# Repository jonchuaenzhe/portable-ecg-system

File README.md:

Jan 2020 - Dec 2020
# IoT-enabled Portable 12-Lead ECG System

12-Lead ECGs are usually bulky and mounted on carts. This project in collaboration with NUH Emergency Department developed a portable version of it which displayed ECG tracings on a web-app to increase the efficiency of clinicians and comfort of patients. Take a look at the video below for a short demo of the system.

https://user-images.githubusercontent.com/59247141/186677922-14ab5f33-408b-436f-be4c-0afafe76f2a2.mp4

## Device

The Schematics and Layout of the circuit board design can be viewed directly in the "device" folder as PDF files.

"main.cpp" contains the firmware for the device, which runs on an ESP32 chip. It requires some commonly used ESP32 libraries not included in the "device" folder.

## Web Dashboard

The "app" folder houses both the client and server components of the MERN stack.

### Installation

Install dependencies for frontend by entering the frontend folder and running:
```
yarn install
```
Install dependencies for backend by entering the backend folder and running:
```
npm install
```

### Running Locally

To start the frontend application, enter the frontend folder and run:
```
yarn start
```
This runs the app in the development mode. Open [http://localhost:3000](http://localhost:3000) to view it in the browser. The page will reload if you make edits. You will also see any lint errors in the console.

To start the backend application, enter the backend folder on a separate terminal and run:
```
npm dev
```

### Deploying

The entire stack is deployed using Docker. Docker images are uploaded onto DockerHub and `docker-compose.prd.yml` is uploaded onto the server. To deploy the application, ssh into the server and run the docker-compose file:
```
ssh root@128.199.106.255
docker-compose -f docker-compose.prd.yml up -d --build
```

This will create a "docker network" and attach the three running containers (consisting of the client listening at port `3000`, server listening at port `5000` and mongo database listening at port `27017` on `mongo`) to it.

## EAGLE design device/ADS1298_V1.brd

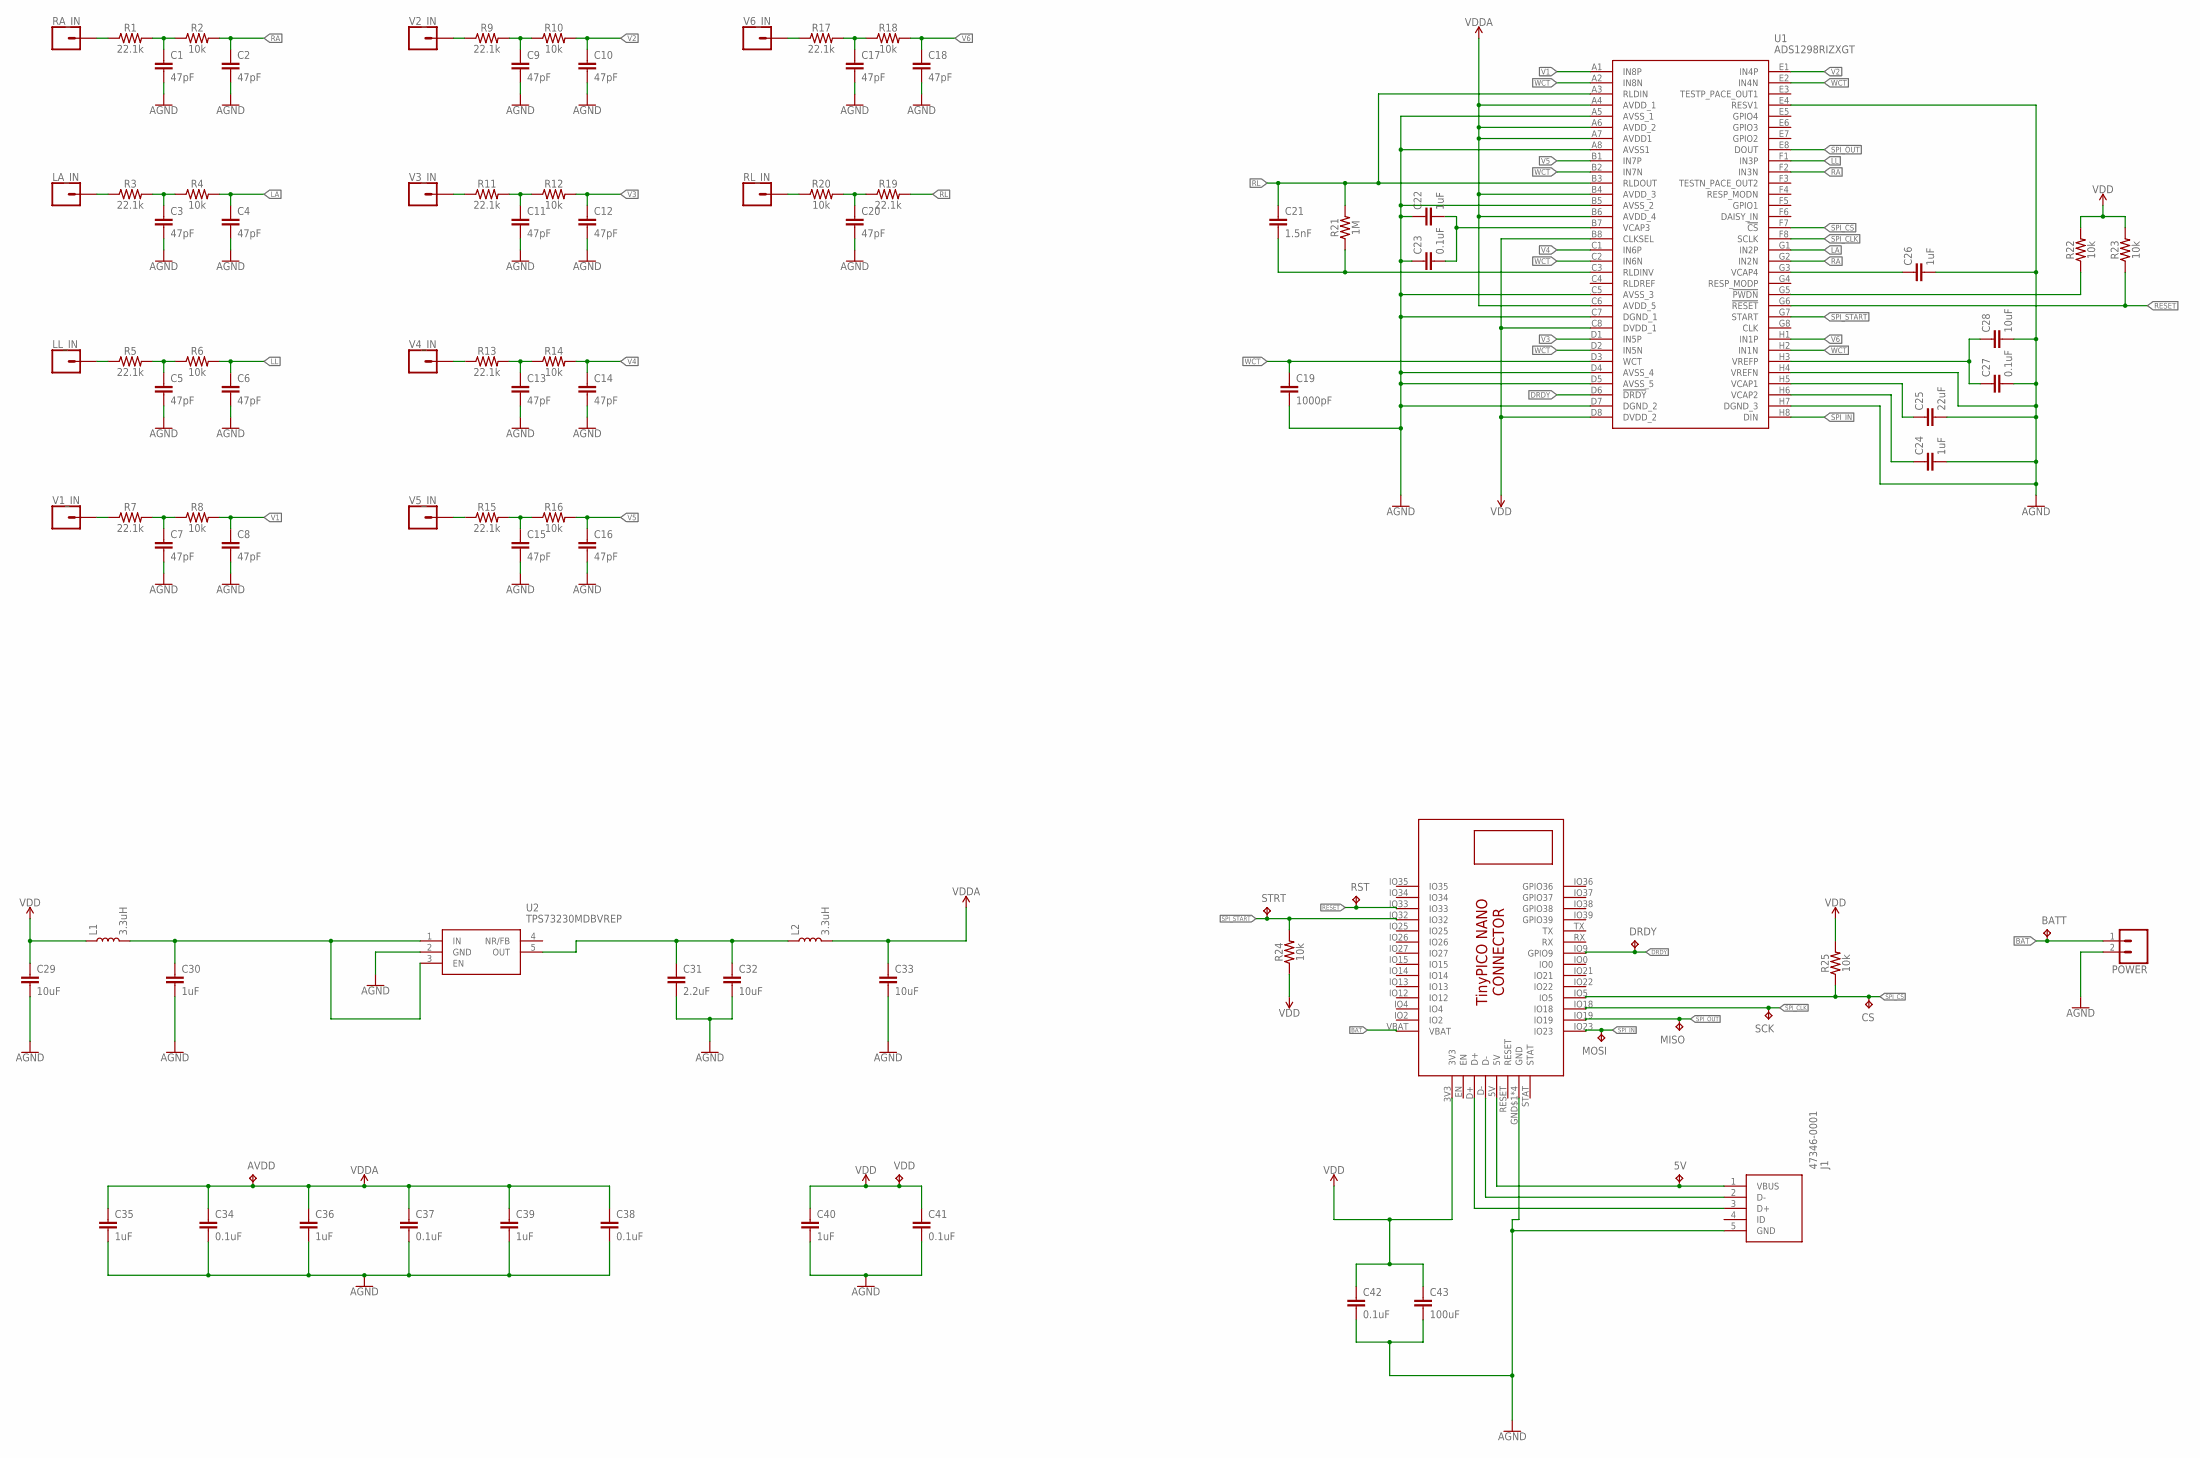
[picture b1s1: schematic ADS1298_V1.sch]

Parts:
5V: TPB1,27; B1,27
AVDD: TPB1,27; B1,27
BATT: TPB1,27; B1,27
C1, C2, C3, C4, C5, C6, C7, C8, C9, C10, C11, C12, C13, C14, C15, C16, C17, C18, C20: 47pF; 0603
C19: 1000pF; 0603
C21: 1.5nF; 0603
C22, C24, C26, C30, C35, C36, C39, C40: 1uF; 0603
C23, C27, C34, C37, C38, C41, C42: 0.1uF; 0603
C25: 22uF; 0805
C28, C29, C32, C33: 10uF; 0805
C31: 2.2uF; 0603
C43: 100uF; 0805
CS: TPB1,27; B1,27
DRDY: TPB1,27; B1,27
J1: 47346-0001
L1, L2: 3.3uH; 0805
LA_IN: CONN_01; 1X01
LL_IN: CONN_01; 1X01
MISO: TPB1,27; B1,27
MOSI: TPB1,27; B1,27
POWER: CONN_02; 1X02
R1, R3, R5, R7, R9, R11, R13, R15, R17, R19: 22.1k; 0603
R2, R4, R6, R8, R10, R12, R14, R16, R18, R20, R22, R23, R24, R25: 10k; 0603
R21: 1M; 0603
RA_IN: CONN_01; 1X01
RL_IN: CONN_01; 1X01
RST: TPB1,27; B1,27
SCK: TPB1,27; B1,27
STRT: TPB1,27; B1,27
U1: ADS1298RIZXGT; BGA64C80P8X8_800X800X145
U2: TPS73230MDBVREP; SOT95P280X145-5N
U3: TINYPICO-NANO-CONNECTOR
V1_IN, V2_IN, V3_IN, V4_IN, V5_IN, V6_IN: CONN_01; 1X01
VDD: TPB1,27; B1,27

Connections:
AGND: C1.2, C2.2, C3.2, C4.2, C5.2, C6.2, C7.2, C8.2, C9.2, C10.2, C11.2, C12.2, C13.2, C14.2, C15.2, C16.2, C17.2, C18.2, C19.2, C20.2, C22.1, C23.1, C24.2, C25.2, C26.2, C27.2, C28.2, C29.2, C30.2, C31.2, C32.2, C33.2, C34.2, C35.2, C36.2, C37.2, C38.2, C39.2, C40.2, C41.2, C42.2, C43.2, J1.5 (GND), POWER.2, U1.A5 (AVSS_1), U1.A8 (AVSS1), U1.B5 (AVSS_2), U1.C5 (AVSS_3), U1.C7 (DGND_1), U1.D4 (AVSS_4), U1.D5 (AVSS_5), U1.D7 (DGND_2), U1.E4 (RESV1), U1.H4 (VREFN), U1.H7 (DGND_3), U2.2 (GND), U3.GND$1 (GND), U3.GND$2 (GND), U3.GND$3 (GND), U3.GND$4 (GND)
BAT: BATT.TP, POWER.1, U3.VBAT
DRDY: DRDY.TP, U1.D6 (!DRDY), U3.IO9 (GPIO9)
LA: C4.1, R4.2, U1.G1 (IN2P)
LL: C6.1, R6.2, U1.F1 (IN3P)
unnamed: R1.1, RA_IN.1
unnamed: C1.1, R1.2, R2.1
unnamed: LA_IN.1, R3.1
unnamed: C3.1, R3.2, R4.1
unnamed: LL_IN.1, R5.1
unnamed: C5.1, R5.2, R6.1
unnamed: R7.1, V1_IN.1
unnamed: C7.1, R7.2, R8.1
unnamed: R9.1, V2_IN.1
unnamed: C9.1, R9.2, R10.1
unnamed: R11.1, V3_IN.1
unnamed: C11.1, R11.2, R12.1
unnamed: R13.1, V4_IN.1
unnamed: C13.1, R13.2, R14.1
unnamed: R15.1, V5_IN.1
unnamed: C15.1, R15.2, R16.1
unnamed: R17.1, V6_IN.1
unnamed: C17.1, R17.2, R18.1
unnamed: R20.1, RL_IN.1
unnamed: C20.1, R19.1, R20.2
unnamed: C21.2, R21.1, U1.C3 (RLDINV)
unnamed: C22.2, C23.2, U1.B7 (VCAP3)
unnamed: R22.1, U1.G5 (!PWDN)
unnamed: C24.1, U1.H6 (VCAP2)
unnamed: C27.1, C28.1, U1.H3 (VREFP)
unnamed: C25.1, U1.H5 (VCAP1)
unnamed: C26.1, U1.G3 (VCAP4)
unnamed: C31.1, C32.1, L2.1, U2.5 (OUT)
unnamed: J1.3 (D+), U3.D+
unnamed: J1.2 (D-), U3.D-
unnamed: 5V.TP, J1.1 (VBUS), U3.5V
unnamed: C30.1, L1.2, U2.1 (IN), U2.3 (EN)
RA: C2.1, R2.2, U1.F2 (IN3N), U1.G2 (IN2N)
RESET: R23.1, RST.TP, U1.G6 (!RESET), U3.IO33
RL: C21.1, R19.2, R21.2, U1.A3 (RLDIN), U1.B3 (RLDOUT)
SPI_CLK: SCK.TP, U1.F8 (SCLK), U3.IO18
SPI_CS: CS.TP, R25.1, U1.F7 (!CS), U3.IO5
SPI_IN: MOSI.TP, U1.H8 (DIN), U3.IO23
SPI_OUT: MISO.TP, U1.E8 (DOUT), U3.IO19
SPI_START: R24.2, STRT.TP, U1.G7 (START), U3.IO32
V1: C8.1, R8.2, U1.A1 (IN8P)
V2: C10.1, R10.2, U1.E1 (IN4P)
V3: C12.1, R12.2, U1.D1 (IN5P)
V4: C14.1, R14.2, U1.C1 (IN6P)
V5: C16.1, R16.2, U1.B1 (IN7P)
V6: C18.1, R18.2, U1.H1 (IN1P)
VDD: C29.1, C40.1, C41.1, C42.1, C43.1, L1.1, R22.2, R23.2, R24.1, R25.2, U1.B8 (CLKSEL), U1.C8 (DVDD_1), U1.D8 (DVDD_2), U3.3V3, VDD.TP
VDDA: AVDD.TP, C33.1, C34.1, C35.1, C36.1, C37.1, C38.1, C39.1, L2.2, U1.A4 (AVDD_1), U1.A6 (AVDD_2), U1.A7 (AVDD1), U1.B4 (AVDD_3), U1.B6 (AVDD_4), U1.C6 (AVDD_5)
WCT: C19.1, U1.A2 (IN8N), U1.B2 (IN7N), U1.C2 (IN6N), U1.D2 (IN5N), U1.D3 (WCT), U1.E2 (IN4N), U1.H2 (IN1N)

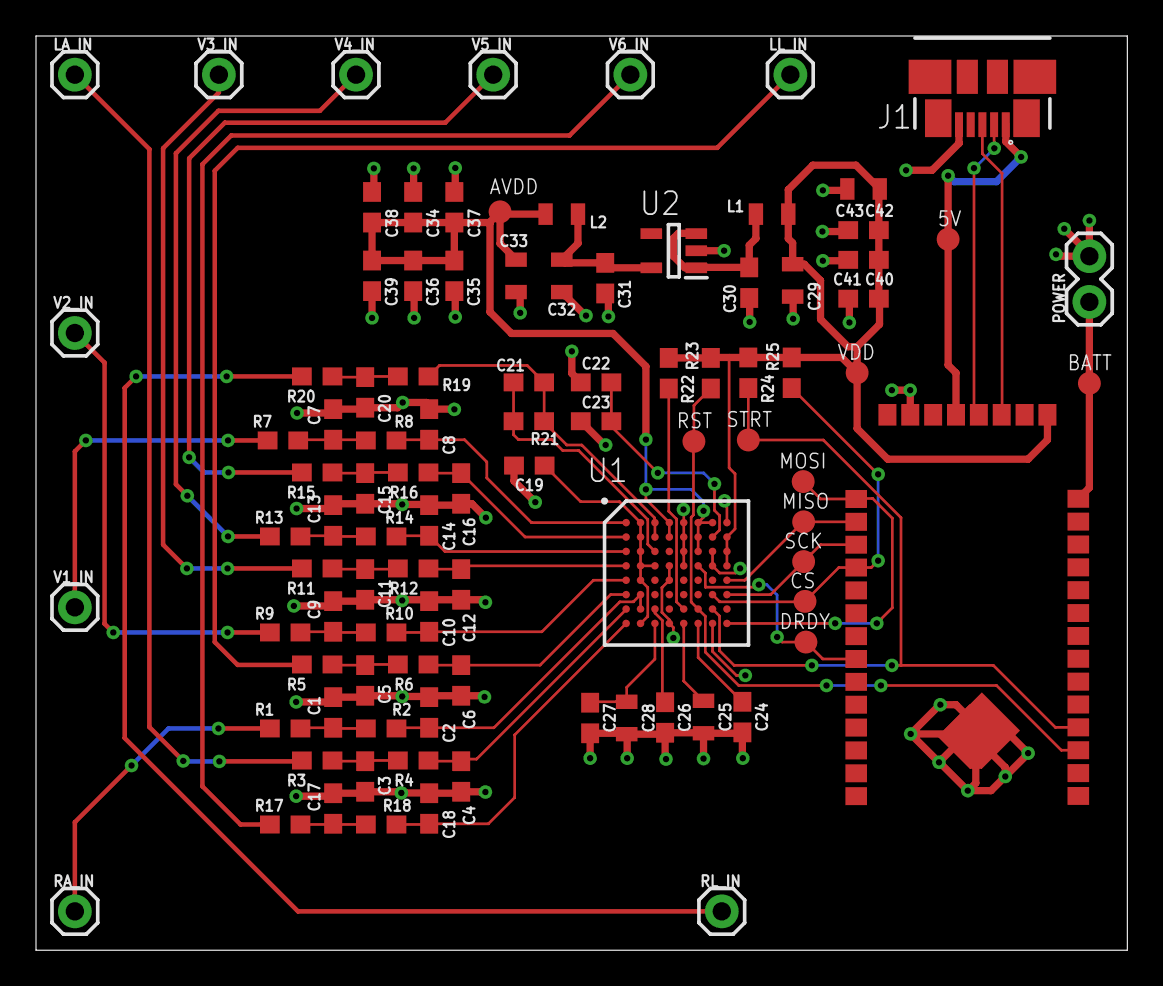
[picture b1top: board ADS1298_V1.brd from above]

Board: 2 copper layers, 60.6 x 50.8 mm, 96 parts (0 on the bottom side), 54 nets.

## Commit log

2022-08-25 added files
2022-08-25 modified readme

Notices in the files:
parts and their libraries:
SparkFun-Capacitors: Licensing: Creative Commons ShareAlike 4.0 International - https://creativecommons.org/licenses/by-sa/4.0
